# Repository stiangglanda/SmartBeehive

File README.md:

<h1 align="center">SmartBeehive Monitoring System</h1>

This project is an IoT-based beehive monitoring system. An ESP32-S3 collects real-time beehive data (weight, temperature, audio, and images) and sends it over Wi-Fi to a central STM32MP215F-DK Linux server running Docker.

<p align="center">
  <a href="https://www.youtube.com/watch?v=g_EhRMFEKto">
    
    <br>
    ▶ Watch Video
  </a>
</p>

## PCB

## Schematic

## Project Structure

This project is divided into two main components:
* **firmware(this Repo)**: The ESP-IDF C source code for the ESP32-S3 edge node.
* **[Web Dashboard](https://github.com/stiangglanda/smart-beehive-dashboard)**: The static Next.js frontend application used to visualize the collected hive metrics and media.

## System Architecture

```mermaid
graph TD
    subgraph ESP32-S3 [ESP32-S3 Beehive Node]
        S_Scale[HX711 Load Cell] --> ESP[ESP32-S3]
        S_Temp[SHT31 Sensor] --> ESP
        S_Probe[DS18B20 Probe] --> ESP
        S_Mic[INMP441 Mic] --> ESP
        S_Cam[OV2640 Cam] --> ESP
        ESP --> Disp[SSD1306 OLED]
    end

    subgraph Server [Any Linux Server - Docker]
        Broker[Mosquitto MQTT]
        NodeRED[Node-RED]
        Influx[InfluxDB v2]
        Nginx[Nginx Web Server]
        Storage[(Shared File Storage)]
    end

    ESP -->|1. MQTT Telemetry| Broker
    Broker -->|2. Forward Data| NodeRED
    NodeRED -->|3. Write Metrics| Influx
    
    ESP -->|4. HTTP POST Images/Audio| NodeRED
    NodeRED -->|5. Save Files| Storage
    Nginx -->|6. Serve Files| Storage
    
    NodeRED -->|7. MQTT Commands| Broker
    Broker -->|8. Forward Commands| ESP

    subgraph Clients [Dashboard Clients]
        UI[Web Dashboard] -->|Fetch /data.json & /history.json| Nginx
        UI -->|Fetch /images & /audio| Nginx
    end
```

## Hardware Components

### Edge Node
* ESP32-S3 development board
* OV2640 Camera
* INMP441 I2S Microphone
* HX711 ADC & Load Cell
* SHT31-D Temp & Humidity Sensor
* DS18B20 Temp Probe
* SSD1306 OLED Display

### Server Host
* **STM32MP215F-DK** (or any device running Linux like Raspberry Pi, PC, or VPS)

## Pinout Mapping (ESP32-S3)

| Component / Signal | ESP32-S3 Pin |
| :--- | :--- |
| **HX711 DOUT** | GPIO 1 |
| **HX711 SCK** | GPIO 2 |
| **I2C SDA** (SHT31 & OLED) | GPIO 21 |
| **I2C SCL** (SHT31 & OLED) | GPIO 38 |
| **DS18B20 Data** | GPIO 14 |
| **INMP441 I2S WS** | GPIO 39 |
| **INMP441 I2S SCK** | GPIO 40 |
| **INMP441 I2S SD** | GPIO 41 |
| **OV2640 Camera** | Standard DVP pinout |

## Server Deployment

To deploy the entire server stack (Mosquitto, Node-RED, InfluxDB, Nginx) on your Linux host using the provided `server/docker-compose.yml`:

```bash
# Start the stack in background (detached mode)
docker-compose up -d

# Verify that all 4 containers are successfully running
docker ps
```

## Edge Node Build Guide

### Configure Credentials
Update the configuration section at the top of the main source file:

```c
#define WIFI_SSID           "Your_SSID"
#define WIFI_PASS           "Your_Password"
#define SERVER_IP           "Your_Server_IP"
```

### Compile and Flash
Execute the following commands in your ESP-IDF terminal environment:

```bash
idf.py set-target esp32s3

idf.py build

idf.py flash
```

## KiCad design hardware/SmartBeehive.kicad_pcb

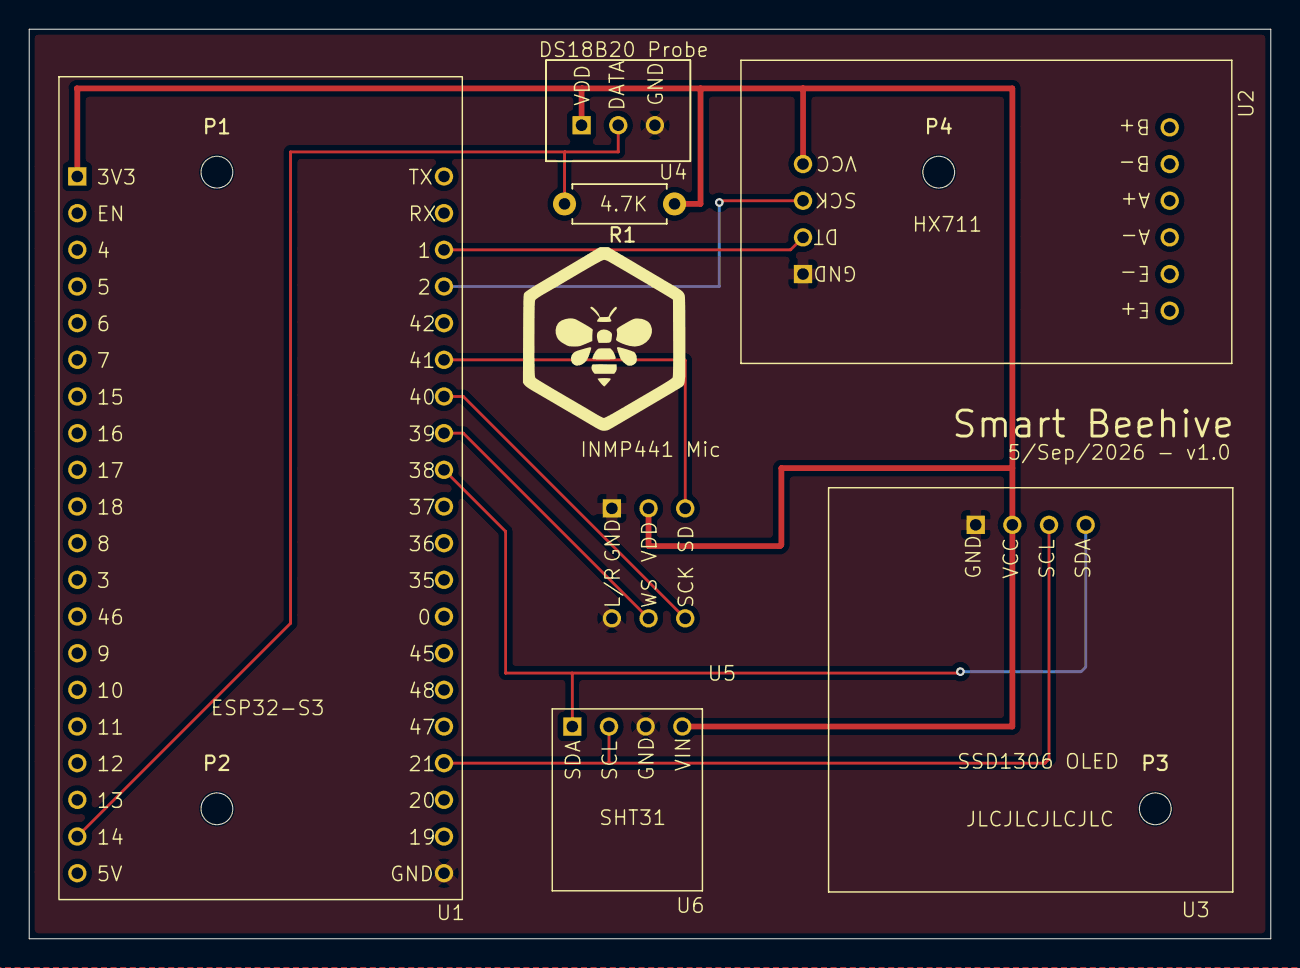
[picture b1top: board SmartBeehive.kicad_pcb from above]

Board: 4 copper layers, 86.0 x 63.0 mm, 11 parts (0 on the bottom side), 10 nets.

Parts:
P1, P2, P3, P4: MountingHole_2.2mm_M2
R1: 4.7K; R_Axial_DIN0207_L6.3mm_D2.5mm_P7.62mm_Horizontal
U1: Freenove_ESP32_S3
U2: HX711_Module; HX711_V2
U3: SSD1306
U4: DS18B20
U5: INMP441
U6: SHT31

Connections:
+3V3: R1.1, U1.1 (3V3), U2.4 (VCC), U3.2 (VCC), U4.1 (VDD), U5.2 (VDD), U6.4 (VIN)
GND: U1.40 (GND), U2.1 (GND), U3.1 (GND), U4.3 (GND), U5.1 (GND), U5.4 (L/R), U6.3 (GND)
unnamed: U1.23 (GPIO1), U2.2 (DT)
unnamed: U1.24 (GPIO2), U2.3 (SCK)
unnamed: R1.2, U1.19 (GPIO14), U4.2 (DATA)
unnamed: U1.37 (GPIO21), U3.3 (SCL), U6.2 (SCL)
unnamed: U1.29 (GPIO38), U3.4 (SDA), U6.1 (SDA)
unnamed: U1.28 (GPIO39), U5.5 (WS)
unnamed: U1.27 (GPIO40), U5.6 (SCK)
unnamed: U1.26 (GPIO41), U5.3 (SD)
